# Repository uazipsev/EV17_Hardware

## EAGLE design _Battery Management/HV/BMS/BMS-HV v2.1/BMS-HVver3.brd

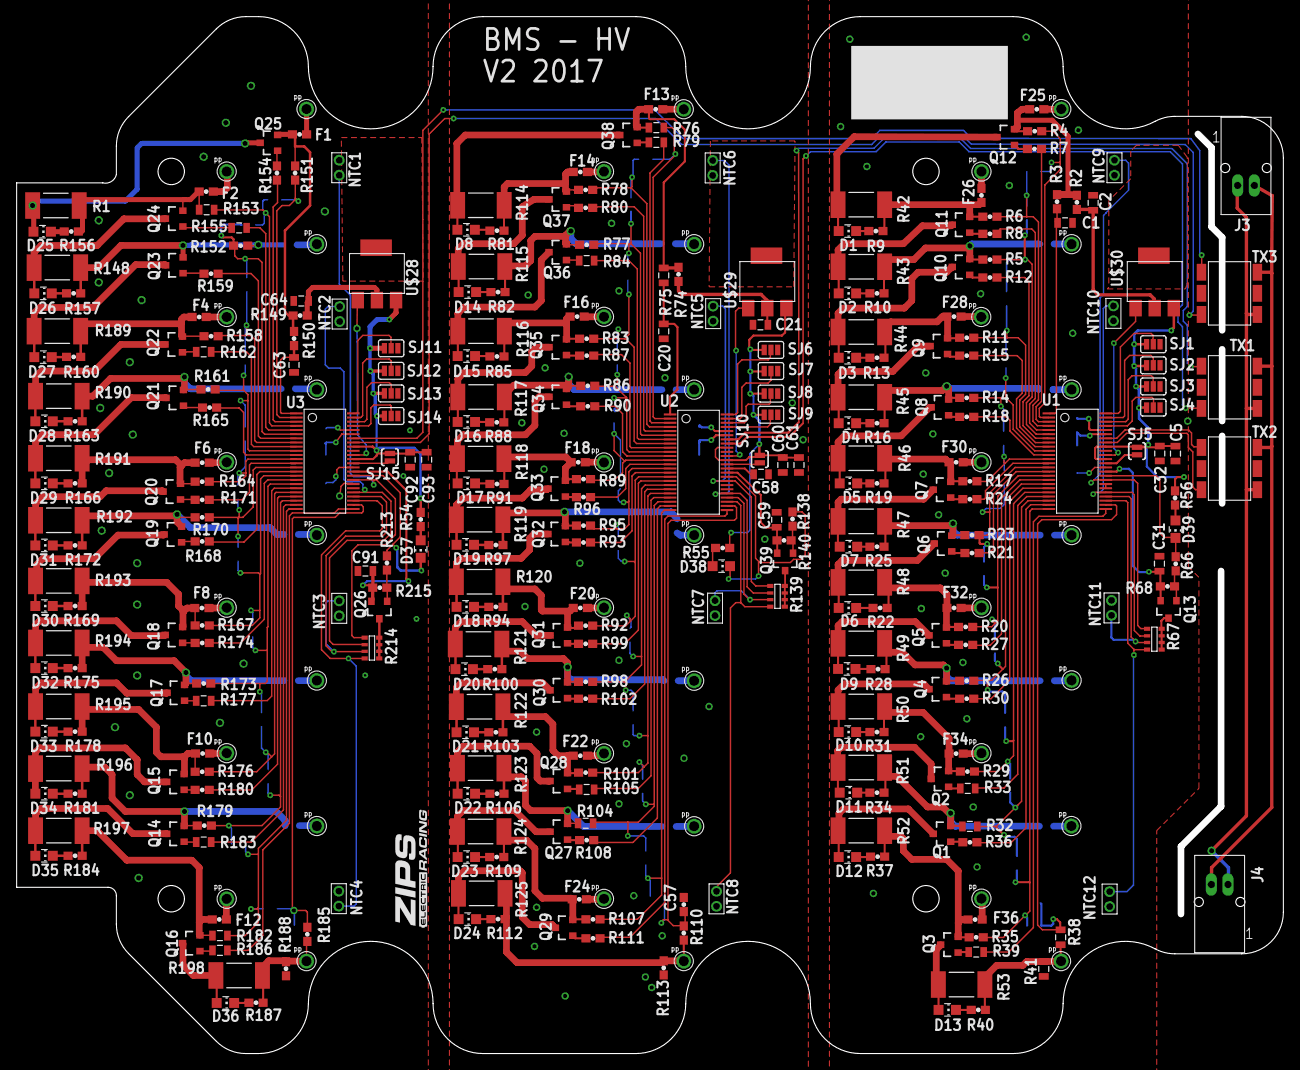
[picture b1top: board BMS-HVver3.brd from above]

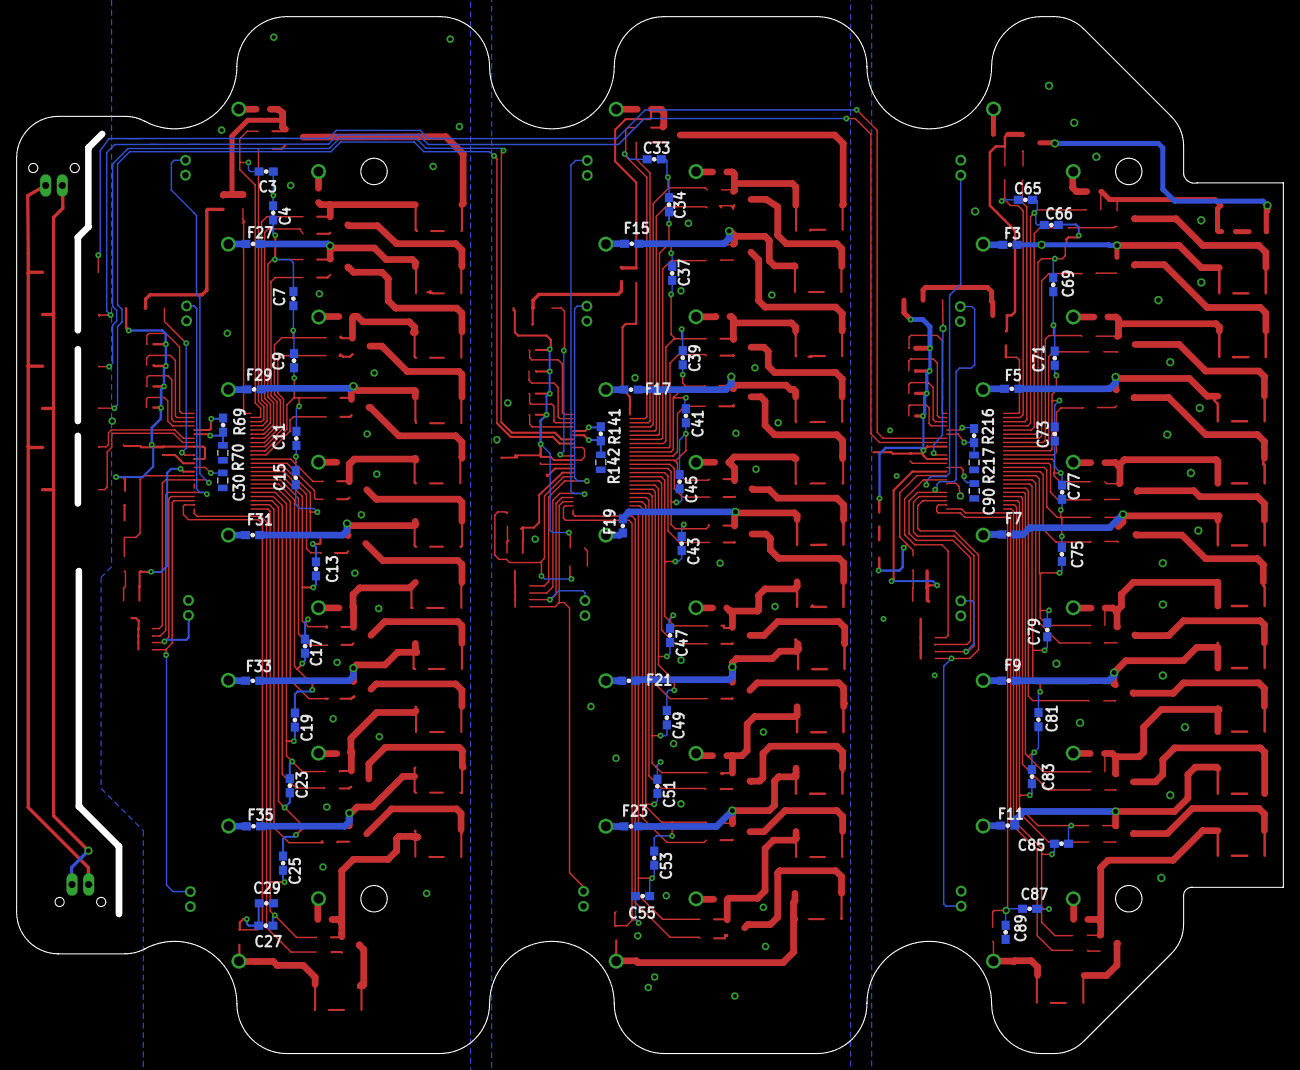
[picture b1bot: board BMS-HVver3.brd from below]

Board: 2 copper layers, 152.4 x 124.8 mm, 423 parts (61 on the bottom side), 332 nets.

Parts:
C1, C2, C20, C21, C63, C64: 0.1UF; 0805
C3, C4, C7, C9, C11, C13, C15, C17, C19, C23, C25, C27, C29, C33, C34, C37, C39, C41, C43, C45, C47, C49, C51, C53, C55, C57, C65, C66, C69, C71, C73, C75, C77, C79, C81, C83, C85, C87, C89: 10NF; 0603
C5, C30, C31, C32, C58, C59, C60, C61, C90, C91, C92, C93: 1UF; 0805
D1, D2, D3, D4, D5, D6, D7, D8, D9, D10, D11, D12, D13, D14, D15, D16, D17, D18, D19, D20, D21, D22, D23, D24, D25, D26, D27, D28, D29, D30, D31, D32, D33, D34, D35, D36: LED_RED; CHIP_LED0805
D37, D38, D39: LED_AMBER; CHIP_LED0805
F1, F2, F3, F4, F5, F6, F7, F8, F9, F10, F11, F12, F13, F14, F15, F16, F17, F18, F19, F20, F21, F22, F23, F24, F25, F26, F27, F28, F29, F30, F31, F32, F33, F34, F35, F36: FUSE_750MA_63V_0603; 0603
J3, J4: M2S02B-PASK-2(LF)(SN); S02B-PASK-2(LF)(SN)
NTC1, NTC2, NTC3, NTC4, NTC5, NTC6, NTC7, NTC8, NTC9, NTC10, NTC11, NTC12: 103JT-025
Q1, Q2, Q3, Q4, Q5, Q6, Q7, Q8, Q9, Q10, Q11, Q12, Q13, Q14, Q15, Q16, Q17, Q18, Q19, Q20, Q21, Q22, Q23, Q24, Q25, Q26, Q27, Q28, Q29, Q30, Q31, Q32, Q33, Q34, Q35, Q36, Q37, Q38, Q39: BSS308PE; SOT23
R1, R42, R43, R44, R45, R46, R47, R48, R49, R50, R51, R52, R53, R114, R115, R116, R117, R118, R119, R120, R121, R122, R123, R124, R125, R148, R189, R190, R191, R192, R193, R194, R195, R196, R197, R198: R2512
R2, R3, R4, R5, R6, R11, R14, R17, R20, R23, R26, R29, R35, R74, R77, R78, R83, R86, R89, R92, R95, R98, R101, R107, R110, R149, R150, R151, R152, R158, R161, R164, R167, R170, R173, R176, R179, R185: 100; 0603
R7, R8, R12, R15, R18, R21, R24, R27, R30, R36, R80, R87, R90, R93, R96, R99, R102, R108, R111, R154, R159, R165, R168, R171, R174, R180: 3.3K; 0603
R9, R10, R13, R16, R19, R22, R25, R28, R31, R34, R37, R40, R81, R82, R85, R88, R91, R94, R97, R100, R103, R106, R109, R112, R156, R157, R160, R163, R166, R169, R172, R175, R178, R181, R184, R187: 475; 0603
R32, R38, R75, R76, R104, R153, R182: 100; 0805
R33, R39, R79, R84, R105, R155, R162, R177, R183, R186: 3.3K; 0805
R41: 0; 0805
R54, R55, R56: 1k; 0603
R66, R138, R213: 1K; 0603
R67, R139, R214: 10K; MNR14
R68, R140, R215: 100K; 0603
R69, R141, R216: 1.2K; 0603
R70, R142, R217: 787; 0805
R113, R188: 0; 0603
SJ1, SJ2, SJ3, SJ4, SJ6, SJ7, SJ8, SJ9, SJ11, SJ12, SJ13, SJ14: PAD-JUMPER-3-NO_YES_SILK
SJ5, SJ10, SJ15: PAD-JUMPER-2-NO_YES_SILK
TX1, TX2, TX3: PE-68386NLT
U1, U2, U3: LTC6804-2; SSOP-48
U$1, U$2, U$3, U$4, U$5, U$6, U$7, U$8, U$9, U$10, U$11, U$12, U$13, U$14, U$15, U$16, U$17, U$18, U$19, U$20, U$21, U$22, U$23, U$24, U$25, U$26, U$40, U$41, U$42, U$43, U$44, U$45, U$46, U$47, U$48, U$49, U$50, U$51, U$52: POGOPIN
U$27: LOGO16-2-L; 2016-2-LOGO-L
U$28, U$29, U$30: NSV1C201MZ4T1G; SOT223

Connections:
A0: SJ9.2, U2.45
A1: SJ8.2, U2.46
A2: SJ7.2, U2.47
A3: SJ6.2, U2.48
A4: SJ4.2, U1.45
A5: SJ3.2, U1.46
A6: SJ2.2, U1.47
A7: SJ1.2, U1.48
A8: SJ14.2, U3.45
A9: SJ13.2, U3.46
A10: SJ12.2, U3.47
A11: SJ11.2, U3.48
C0: C55.2, C57.1, R110.2, U2.26
C1: C53.2, C55.1, R107.2, U2.24
C2: C51.2, C53.1, R104.2, U2.22
C3: C49.2, C51.1, R101.2, U2.20
C4: C47.2, C49.1, R98.2, U2.18
C5: C43.2, C47.1, R92.2, U2.16
C6: C43.1, C45.2, R95.2, U2.14
C7: C41.2, C45.1, R89.2, U2.12
C8: C39.2, C41.1, R86.2, U2.10
C9: C37.2, C39.1, R83.2, U2.8
C10: C34.2, C37.1, R77.2, U2.6
C11: C33.2, C34.1, R78.2, U2.4
C12: C33.1, R76.2, U2.2
C13: C3.1, R4.2, U1.2
C14: C3.2, C4.1, R6.2, U1.4
C15: C7.2, C9.1, R11.2, U1.8
C16: C11.2, C15.1, R17.2, U1.12
C17: C13.1, C15.2, R23.2, U1.14
C18: C13.2, C17.1, R20.2, U1.16
C19: C19.2, C23.1, R29.2, U1.20
C20: C23.2, C25.1, R32.2, U1.22
C21: C25.2, C27.1, R35.2, U1.24
C22: C4.2, C7.1, R5.2, U1.6
C23: C27.2, C29.1, R38.2, U1.26
C24: C17.2, C19.1, R26.2, U1.18
C25: C9.2, C11.1, R14.2, U1.10
C26: C65.1, R151.2, U3.2
C27: C65.2, C66.1, R153.2, U3.4
C28: C69.2, C71.1, R158.2, U3.8
C29: C73.2, C77.1, R164.2, U3.12
C30: C75.1, C77.2, R170.2, U3.14
C31: C75.2, C79.1, R167.2, U3.16
C32: C81.2, C83.1, R176.2, U3.20
C33: C83.2, C85.1, R179.2, U3.22
C34: C85.2, C87.1, R182.2, U3.24
C35: C66.2, C69.1, R152.2, U3.6
C36: C87.2, C89.1, R185.2, U3.26
C37: C79.2, C81.1, R173.2, U3.18
C38: C71.2, C73.1, R161.2, U3.10
DRIVE: U2.38, U$29.P$1
DRIVE1: U1.38, U$30.P$1
DRIVE2: U3.38, U$28.P$1
GND: C63.2, C64.2, C89.2, C90.2, C91.2, C92.2, C93.2, NTC1.1, NTC2.1, NTC3.1, NTC4.1, R188.2, R217.1, SJ11.3, SJ12.3, SJ13.3, SJ14.3, U3.30, U3.31
GNDA: C20.2, C21.2, C57.2, C58.2, C59.2, C60.2, C61.2, NTC5.1, NTC6.1, NTC7.1, R113.2, R142.1, SJ6.3, SJ7.3, SJ8.3, SJ9.3, U2.30, U2.31
GNDI: C1.2, C2.2, C5.2, C29.2, C30.2, C31.2, C32.2, NTC9.1, NTC10.1, NTC11.1, NTC12.1, R41.2, R70.1, SJ1.3, SJ2.3, SJ3.3, SJ4.3, U1.30, U1.31
GPIO1: NTC8.2, R139.4, U2.27
GPIO2: NTC7.2, R139.3, U2.28
GPIO3: NTC6.2, R139.2, U2.29
GPIO4: NTC5.2, R139.1, U2.32
GPIO5: D38.C, R138.2, U2.33
GPIO6: NTC10.2, R67.2, U1.29
GPIO7: NTC9.2, R67.1, U1.32
GPIO8: NTC12.2, R67.4, U1.27
GPIO9: NTC11.2, R67.3, U1.28
GPIO10: D39.C, R66.2, U1.33
GPIO11: NTC2.2, R214.2, U3.29
GPIO12: NTC1.2, R214.1, U3.32
GPIO13: NTC4.2, R214.4, U3.27
GPIO14: NTC3.2, R214.3, U3.28
GPIO15: D37.C, R213.2, U3.33
IBIAS: R141.2, U2.44
IBIAS1: R69.2, U1.44
IBIAS2: R216.2, U3.44
ICMP: R141.1, R142.2, U2.43
ICMP1: R69.1, R70.2, U1.43
ICMP2: R216.1, R217.2, U3.43
IMA: TX1.3, U2.41
IMA1: TX2.3, U1.41
IMA2: TX3.3, U3.41
IPA: TX1.1, U2.42
IPA1: TX2.1, U1.42
IPA2: TX3.1, U3.42
unnamed: Q12.1, R7.1
unnamed: D1.A, Q12.3, R42.2
unnamed: D1.C, R9.2
unnamed: F26.2, Q11.2, R6.1, R9.1, R42.1
unnamed: Q11.1, R8.1
unnamed: D2.A, Q11.3, R43.2
unnamed: D2.C, R10.2
unnamed: F27.2, Q10.2, R5.1, R10.1, R43.1
unnamed: Q10.1, R12.1
unnamed: D3.A, Q10.3, R44.2
unnamed: D3.C, R13.2
unnamed: F28.2, Q9.2, R11.1, R13.1, R44.1
unnamed: Q9.1, R15.1
unnamed: D4.A, Q9.3, R45.2
unnamed: D4.C, R16.2
unnamed: F29.2, Q8.2, R14.1, R16.1, R45.1
unnamed: Q8.1, R18.1
unnamed: D5.A, Q8.3, R46.2
unnamed: D5.C, R19.2
unnamed: Q6.1, R21.1
unnamed: D6.A, Q6.3, R48.2
unnamed: D6.C, R22.2
unnamed: F30.2, Q7.2, R17.1, R19.1, R46.1
unnamed: Q7.1, R24.1
unnamed: D7.A, Q7.3, R47.2
unnamed: D7.C, R25.2
unnamed: F31.2, Q6.2, R23.1, R25.1, R47.1
unnamed: F32.2, Q5.2, R20.1, R22.1, R48.1
unnamed: Q5.1, R27.1
unnamed: D9.A, Q5.3, R49.2
unnamed: D9.C, R28.2
unnamed: F33.2, Q4.2, R26.1, R28.1, R49.1
unnamed: Q4.1, R30.1
unnamed: D10.A, Q4.3, R50.2
unnamed: D10.C, R31.2
unnamed: F34.2, Q2.2, R29.1, R31.1, R50.1
unnamed: Q2.1, R33.1
unnamed: D11.A, Q2.3, R51.2
unnamed: D11.C, R34.2
unnamed: F35.2, Q1.2, R32.1, R34.1, R51.1
unnamed: Q1.1, R36.1
unnamed: D12.A, Q1.3, R52.2
unnamed: D12.C, R37.2
unnamed: Q3.1, R39.1
unnamed: D13.C, R40.2
unnamed: F25.2, Q12.2, R2.1, R3.1, R4.1
unnamed: D13.A, Q3.3, R53.2
unnamed: R38.1, R40.1, R41.1, R53.1, U$1.1
unnamed: F36.2, Q3.2, R35.1, R37.1, R52.1
unnamed: C2.1, R2.2, U$30.P$2
unnamed: Q13.3, R67.5, R67.6, R67.7, R67.8
unnamed: Q13.1, R66.1, R68.1
unnamed: Q25.1, R154.1
unnamed: D25.A, Q25.3, R1.2
unnamed: D25.C, R156.2
unnamed: F2.2, Q24.2, R1.1, R153.1, R156.1
unnamed: Q24.1, R155.1
unnamed: D26.A, Q24.3, R148.2
unnamed: D26.C, R157.2
unnamed: F3.2, Q23.2, R148.1, R152.1, R157.1
unnamed: Q23.1, R159.1
unnamed: D27.A, Q23.3, R189.2
unnamed: D27.C, R160.2
unnamed: F4.2, Q22.2, R158.1, R160.1, R189.1
unnamed: Q22.1, R162.1
unnamed: D28.A, Q22.3, R190.2
unnamed: D28.C, R163.2
unnamed: F5.2, Q21.2, R161.1, R163.1, R190.1
unnamed: Q21.1, R165.1
unnamed: D29.A, Q21.3, R191.2
unnamed: D29.C, R166.2
unnamed: Q19.1, R168.1
unnamed: D30.A, Q19.3, R193.2
unnamed: D30.C, R169.2
unnamed: F6.2, Q20.2, R164.1, R166.1, R191.1
unnamed: Q20.1, R171.1
unnamed: D31.A, Q20.3, R192.2
unnamed: D31.C, R172.2
unnamed: F7.2, Q19.2, R170.1, R172.1, R192.1
unnamed: F8.2, Q18.2, R167.1, R169.1, R193.1
unnamed: Q18.1, R174.1
unnamed: D32.A, Q18.3, R194.2
unnamed: D32.C, R175.2
unnamed: F9.2, Q17.2, R173.1, R175.1, R194.1
unnamed: Q17.1, R177.1
unnamed: D33.A, Q17.3, R195.2
unnamed: D33.C, R178.2
unnamed: F10.2, Q15.2, R176.1, R178.1, R195.1
unnamed: Q15.1, R180.1
unnamed: D34.A, Q15.3, R196.2
unnamed: D34.C, R181.2
unnamed: F11.2, Q14.2, R179.1, R181.1, R196.1
unnamed: Q14.1, R183.1
unnamed: D35.A, Q14.3, R197.2
unnamed: D35.C, R184.2
unnamed: Q16.1, R186.1
unnamed: D36.C, R187.2
unnamed: F1.2, Q25.2, R149.1, R150.1, R151.1
unnamed: D36.A, Q16.3, R198.2
unnamed: Q38.1, R79.1
unnamed: D8.A, Q38.3, R114.2
unnamed: D8.C, R81.2
unnamed: R185.1, R187.1, R188.1, R198.1, U$14.1
unnamed: F12.2, Q16.2, R182.1, R184.1, R197.1
unnamed: C64.1, R149.2, U$28.P$2
unnamed: F14.2, Q37.2, R78.1, R81.1, R114.1
unnamed: D37.A, R54.1
unnamed: Q37.1, R80.1
unnamed: D14.A, Q37.3, R115.2
unnamed: D14.C, R82.2
unnamed: F15.2, Q36.2, R77.1, R82.1, R115.1
unnamed: Q26.3, R214.5, R214.6, R214.7, R214.8
unnamed: Q36.1, R84.1
unnamed: D15.A, Q36.3, R116.2
unnamed: D15.C, R85.2
unnamed: F16.2, Q35.2, R83.1, R85.1, R116.1
unnamed: Q26.1, R213.1, R215.1
unnamed: D38.A, R55.1
unnamed: Q35.1, R87.1
unnamed: D16.A, Q35.3, R117.2
unnamed: D16.C, R88.2
unnamed: F17.2, Q34.2, R86.1, R88.1, R117.1
unnamed: J3.2, J4.2, TX1.6, TX2.6, TX3.6
unnamed: Q34.1, R90.1
unnamed: D17.A, Q34.3, R118.2
unnamed: D17.C, R91.2
unnamed: J3.1, J4.1, TX1.4, TX2.4, TX3.4
unnamed: Q32.1, R93.1
unnamed: D18.A, Q32.3, R120.2
unnamed: D18.C, R94.2
unnamed: C90.1, U3.35
unnamed: F18.2, Q33.2, R89.1, R91.1, R118.1
unnamed: C30.1, U1.35
unnamed: Q33.1, R96.1
unnamed: D19.A, Q33.3, R119.2
unnamed: D19.C, R97.2
unnamed: F19.2, Q32.2, R95.1, R97.1, R119.1
unnamed: D39.A, R56.1
unnamed: F20.2, Q31.2, R92.1, R94.1, R120.1
unnamed: Q31.1, R99.1
unnamed: D20.A, Q31.3, R121.2
unnamed: D20.C, R100.2
unnamed: F21.2, Q30.2, R98.1, R100.1, R121.1
unnamed: Q30.1, R102.1
unnamed: D21.A, Q30.3, R122.2
unnamed: D21.C, R103.2
unnamed: F22.2, Q28.2, R101.1, R103.1, R122.1
unnamed: Q28.1, R105.1
unnamed: D22.A, Q28.3, R123.2
unnamed: D22.C, R106.2
unnamed: F23.2, Q27.2, R104.1, R106.1, R123.1
unnamed: Q27.1, R108.1
unnamed: D23.A, Q27.3, R124.2
unnamed: D23.C, R109.2
unnamed: Q29.1, R111.1
unnamed: D24.C, R112.2
unnamed: F13.2, Q38.2, R74.1, R75.1, R76.1
unnamed: D24.A, Q29.3, R125.2
unnamed: R110.1, R112.1, R113.1, R125.1, U$40.1
unnamed: F24.2, Q29.2, R107.1, R109.1, R124.1
unnamed: C21.1, R74.2, U$29.P$2
unnamed: Q39.3, R139.5, R139.6, R139.7, R139.8
unnamed: Q39.1, R138.1, R140.1
unnamed: F12.1, U$15.1
unnamed: F11.1, U$16.1
unnamed: F10.1, U$17.1
unnamed: F9.1, U$18.1
unnamed: F8.1, U$19.1
unnamed: F7.1, U$20.1
unnamed: F6.1, U$21.1
unnamed: F5.1, U$22.1
unnamed: F4.1, U$23.1
unnamed: F3.1, U$24.1
unnamed: F2.1, U$25.1
unnamed: F1.1, U$26.1
unnamed: F24.1, U$41.1
unnamed: F23.1, U$42.1
unnamed: F22.1, U$43.1
unnamed: F21.1, U$44.1
unnamed: F20.1, U$45.1
unnamed: F19.1, U$46.1
unnamed: F18.1, U$47.1
unnamed: F17.1, U$48.1
unnamed: F16.1, U$49.1
unnamed: F15.1, U$50.1
unnamed: F14.1, U$51.1
unnamed: F13.1, U$52.1
unnamed: F36.1, U$2.1
unnamed: F35.1, U$3.1
unnamed: F34.1, U$4.1
unnamed: F33.1, U$5.1
unnamed: F32.1, U$6.1
unnamed: F31.1, U$7.1
unnamed: F30.1, U$8.1
unnamed: F29.1, U$9.1
unnamed: F28.1, U$10.1
unnamed: F27.1, U$11.1
unnamed: F26.1, U$12.1
unnamed: F25.1, U$13.1
S1: R111.2, U2.25
S2: R108.2, U2.23
S3: R105.2, U2.21
S4: R102.2, U2.19
S5: R99.2, U2.17
S6: R93.2, U2.15
S7: R96.2, U2.13
S8: R90.2, U2.11
S9: R87.2, U2.9
S10: R84.2, U2.7
S11: R80.2, U2.5
S12: R79.2, U2.3
S13: R7.2, U1.3
S14: R8.2, U1.5
S15: R12.2, U1.7
S16: R15.2, U1.9
S17: R18.2, U1.11
S18: R21.2, U1.15
S19: R24.2, U1.13
S20: R27.2, U1.17
S21: R30.2, U1.19
S22: R33.2, U1.21
S23: R36.2, U1.23
S24: R39.2, U1.25
S25: R154.2, U3.3
S26: R155.2, U3.5
S27: R159.2, U3.7
S28: R162.2, U3.9
S29: R165.2, U3.11
S30: R168.2, U3.15
S31: R171.2, U3.13
S32: R174.2, U3.17
S33: R177.2, U3.19
S34: R180.2, U3.21
S35: R183.2, U3.23
S36: R186.2, U3.25
SWTEN: SJ10.1, U2.36
SWTEN1: SJ5.1, U1.36
SWTEN2: SJ15.1, U3.36
V+: C20.1, R75.2, U2.1
V+1: C1.1, R3.2, U1.1
V+2: C63.1, R150.2, U3.1
VREF1: C58.1, U2.35
VREF2: C59.1, Q39.2, R140.2, U2.34
VREF4: C31.1, Q13.2, R68.2, U1.34
VREF6: C91.1, Q26.2, R215.2, U3.34
VREG: C60.1, C61.1, R55.2, SJ6.1, SJ7.1, SJ8.1, SJ9.1, SJ10.2, U2.37, U2.40, U$29.P$3
VREG1: C5.1, C32.1, R56.2, SJ1.1, SJ2.1, SJ3.1, SJ4.1, SJ5.2, U1.37, U1.40, U$30.P$3
VREG2: C92.1, C93.1, R54.2, SJ11.1, SJ12.1, SJ13.1, SJ14.1, SJ15.2, U3.37, U3.40, U$28.P$3

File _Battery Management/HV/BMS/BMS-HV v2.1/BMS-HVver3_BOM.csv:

Qty-1,Part References,Value,Package,Mfg Part Num,Mfg Name,VID,Vendor Part Num,Description,Pkg Code,XREF
3,"SJ5, SJ10, SJ15",,PAD-JUMPER-2-NO_YES_SILK,***PART# '*' NOT FOUND***,*,*,*,*,*,*
12,"SJ1, SJ2, SJ3, SJ4, SJ6, SJ7, SJ8, SJ9, SJ11, SJ12, SJ13, SJ14",,PAD-JUMPER-3-NO_YES_SILK,***PART# '*' NOT FOUND***,*,*,*,*,*,*
36,"R1, R42, R43, R44, R45, R46, R47, R48, R49, R50, R51, R52, R53, R114, R115, R116, R117, R118, R119, R120, R121, R122, R123, R124, R125, R148, R189, R190, R191, R192, R193, R194, R195, R196, R197, R198",,R2512,***PART# '*' NOT FOUND***,*,*,*,*,*,*
2,"R113, R188",0,0603,CRCW06030000Z0EA,Vishay Dale,DK,541-0.0GCT-ND,RES SMD 0.0OHM JUMPER 1/10W 0603,0603 (1608 Metric),REF167
1,"R41",0,0805,RC0805JR-070RL,Yageo,DK,311-0.0ARCT-ND,RES SMD 0.0 OHM JUMPER 1/8W 0805,0805 (2012 Metric),REF310
6,"C1, C2, C20, C21, C63, C64",0.1UF,0805,CL21B104KCC5PNC,Samsung Electro-Mechanics America, Inc.,DK,1276-2447-1-ND,CAP CER 0.1UF 100V X7R 0805,0805 (2012 Metric),REF253
3,"R69, R141, R216",1.2K,0603,RC0603JR-071K2L,Yageo,DK,311-1.2KGRCT-ND,RES SMD 1.2K OHM 5% 1/10W 0603,0603 (1608 Metric),REF88
3,"R66, R138, R213",1K,0603,RC0603JR-071KL,Yageo,DK,311-1.0KGRCT-ND,RES SMD 1K OHM 5% 1/10W 0603,0603 (1608 Metric),REF84
12,"C5, C30, C31, C32, C58, C59, C60, C61, C90, C91, C92, C93",1UF,0805,UMK212F105ZG-T,Taiyo Yuden,DK,587-1308-1-ND,CAP CER 1UF 50V Y5V 0805,0805 (2012 Metric),REF17
3,"R54, R55, R56",1k,0603,RC0603JR-071KL,Yageo,DK,311-1.0KGRCT-ND,RES SMD 1K OHM 5% 1/10W 0603,0603 (1608 Metric),REF84
26,"R7, R8, R12, R15, R18, R21, R24, R27, R30, R36, R80, R87, R90, R93, R96, R99, R102, R108, R111, R154, R159, R165, R168, R171, R174, R180",3.3K,0603,RC0603JR-073K3L,Yageo,DK,311-3.3KGRCT-ND,RES SMD 3.3K OHM 5% 1/10W 0603,0603 (1608 Metric),REF89
10,"R33, R39, R79, R84, R105, R155, R162, R177, R183, R186",3.3K,0805,RC0805FR-073K3L,Yageo,DK,311-3.30KCRCT-ND,RES SMD 3.3K OHM 1% 1/8W 0805,0805 (2012 Metric),REF128
3,"R67, R139, R214",10K,MNR14,MNR14ERAPJ103,Rohm Semiconductor,DK,RHM1596CT-ND,RES ARRAY 4 RES 10K OHM 1206,1206 (3216 Metric), Convex, Long Side Terminals,REF29
39,"C3, C4, C7, C9, C11, C13, C15, C17, C19, C23, C25, C27, C29, C33, C34, C37, C39, C41, C43, C45, C47, C49, C51, C53, C55, C57, C65, C66, C69, C71, C73, C75, C77, C79, C81, C83, C85, C87, C89",10NF,0603,CL10B103KC8NNNC,Samsung Electro-Mechanics America, Inc.,DK,1276-1196-1-ND,CAP CER 10000PF 100V X7R 0603,0603 (1608 Metric),REF160
38,"R2, R3, R4, R5, R6, R11, R14, R17, R20, R23, R26, R29, R35, R74, R77, R78, R83, R86, R89, R92, R95, R98, R101, R107, R110, R149, R150, R151, R152, R158, R161, R164, R167, R170, R173, R176, R179, R185",100,0603,RC0603FR-07100RL,Yageo,DK,311-100HRCT-ND,RES SMD 100 OHM 1% 1/10W 0603,0603 (1608 Metric),REF159
7,"R32, R38, R75, R76, R104, R153, R182",100,0805,RC0805FR-07100RL,Yageo,DK,311-100CRCT-ND,RES SMD 100 OHM 1% 1/8W 0805,0805 (2012 Metric),REF307
3,"R68, R140, R215",100K,0603,RC0603JR-07100KL,Yageo,DK,311-100KGRCT-ND,RES SMD 100K OHM 5% 1/10W 0603,0603 (1608 Metric),REF90
12,"NTC1, NTC2, NTC3, NTC4, NTC5, NTC6, NTC7, NTC8, NTC9, NTC10, NTC11, NTC12",103JT-025,103JT-025,***PART# '*' NOT FOUND***,*,*,*,*,*,*
36,"R9, R10, R13, R16, R19, R22, R25, R28, R31, R34, R37, R40, R81, R82, R85, R88, R91, R94, R97, R100, R103, R106, R109, R112, R156, R157, R160, R163, R166, R169, R172, R175, R178, R181, R184, R187",475,0603,CRCW0201475RFKED,Vishay Dale,DK,541-475AABCT-ND,RES SMD 475 OHM 1% 1/20W 0201,0201 (0603 Metric),REF292
3,"R70, R142, R217",787,0805,RC0805FR-07787RL,Yageo,DK,311-787CRCT-ND,RES SMD 787 OHM 1% 1/8W 0805,0805 (2012 Metric),REF183
39,"Q1, Q2, Q3, Q4, Q5, Q6, Q7, Q8, Q9, Q10, Q11, Q12, Q13, Q14, Q15, Q16, Q17, Q18, Q19, Q20, Q21, Q22, Q23, Q24, Q25, Q26, Q27, Q28, Q29, Q30, Q31, Q32, Q33, Q34, Q35, Q36, Q37, Q38, Q39",BSS308PE,SOT23,BSS308PE H6327,Infineon Technologies,DK,BSS308PE H6327CT-ND,MOSFET P-CH 30V 2A SOT23,SOT-23-3,REF291
36,"F1, F2, F3, F4, F5, F6, F7, F8, F9, F10, F11, F12, F13, F14, F15, F16, F17, F18, F19, F20, F21, F22, F23, F24, F25, F26, F27, F28, F29, F30, F31, F32, F33, F34, F35, F36",FUSE_750MA_63V_0603,0603,C2Q 750,Bel Fuse Inc.,DK,507-1090-1-ND,FUSE BOARD MNT 750MA 32VAC 63VDC,0603 (1608 Metric),REF309
3,"D37, D38, D39",LED_AMBER,CHIP_LED0805,HSMA-C170,Avago Technologies US Inc.,DK,516-1431-1-ND,LED AMBER DIFFUSED 0805 SMD,0805 (2012 Metric),REF39
36,"D1, D2, D3, D4, D5, D6, D7, D8, D9, D10, D11, D12, D13, D14, D15, D16, D17, D18, D19, D20, D21, D22, D23, D24, D25, D26, D27, D28, D29, D30, D31, D32, D33, D34, D35, D36",LED_RED,CHIP_LED0805,LH R974-LP-1,OSRAM Opto Semiconductors Inc.,DK,475-1415-1-ND,LED RED DIFFUSED 0805 SMD,0805 (2012 Metric),REF36
1,"U$27",LOGO16-2-L,2016-2-LOGO-L,***PART# '*' NOT FOUND***,*,*,*,*,*,*
3,"U1, U2, U3",LTC6804-2,SSOP-48,LTC6804IG-2#PBF,Linear Technology,DK,LTC6804IG-2#PBF-ND,IC MONITOR BATT STACK 48SSOP,48-FSOP (0.209", 5.30mm Width),REF215
2,"J3, J4",M2S02B-PASK-2(LF)(SN),S02B-PASK-2(LF)(SN),***PART# 'S02B-PASK-2(LF)(SN)' NOT FOUND***,*,*,*,*,*,*
3,"U$28, U$29, U$30",NSV1C201MZ4T1G,SOT223,***PART# 'NSV1C201MZ4T1G' NOT FOUND***,*,*,*,*,*,*
3,"TX1, TX2, TX3",PE-68386NLT,PE-68386NLT,PE-68386NLT,Pulse Electronics Corporation,DK,553-1776-1-ND,XFRMR GATE DRIVE 1:1 785UH SMD,None,REF166
39,"U$1, U$2, U$3, U$4, U$5, U$6, U$7, U$8, U$9, U$10, U$11, U$12, U$13, U$14, U$15, U$16, U$17, U$18, U$19, U$20, U$21, U$22, U$23, U$24, U$25, U$26, U$40, U$41, U$42, U$43, U$44, U$45, U$46, U$47, U$48, U$49, U$50, U$51, U$52",POGOPIN,POGOPIN,***PART# '*' NOT FOUND***,*,*,*,*,*,*

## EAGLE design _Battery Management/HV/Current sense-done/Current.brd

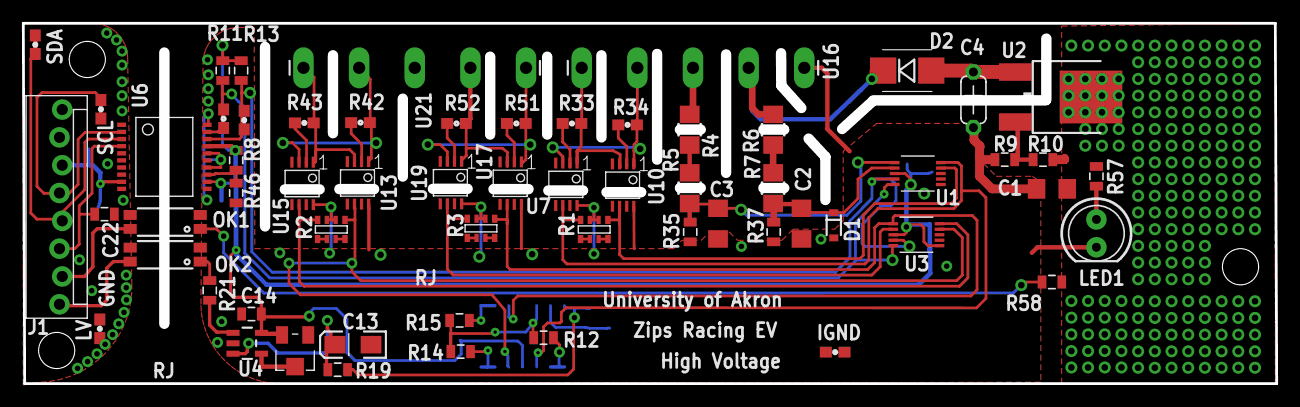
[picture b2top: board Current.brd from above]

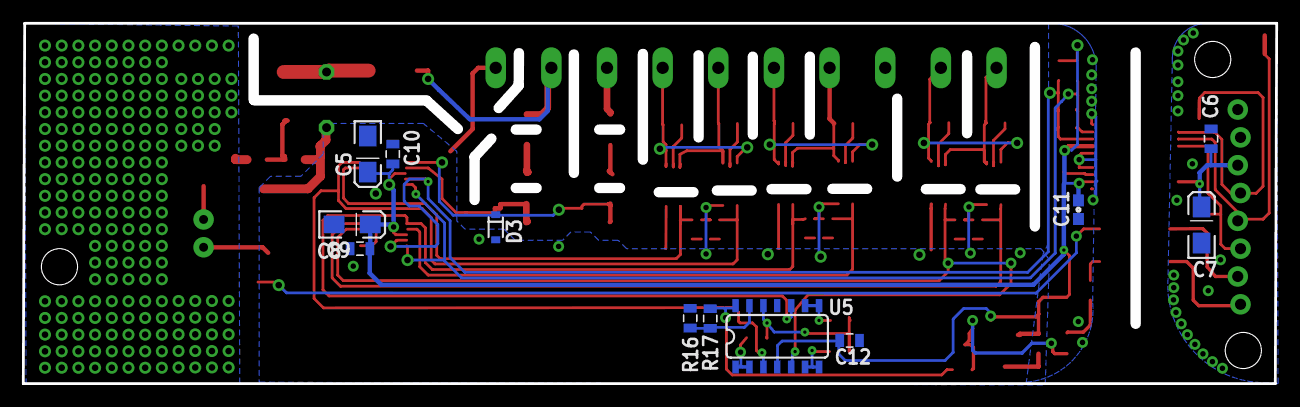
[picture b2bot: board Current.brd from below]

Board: 2 copper layers, 114.4 x 32.9 mm, 77 parts (12 on the bottom side), 57 nets.

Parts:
C1, C2, C3: 10UF; 1206@1
C4: 0.47UF; C_TH_05-02
C5, C7, C9, C13: 10UF; EIA3216-16V
C6, C8, C10, C12, C14, C22: 0.1UF; 0805
C11: 0.01UF; 0603
D1, D3: 3.3V; SOD-323
D2: DIODE-ZENER_56V; SMB
GND: TPSMD; 0603
IGND: TPSMD; 0603
ISCL: TPSMD; 0603
ISDA: TPSMD; 0603
J1: M80022232081-2; MOLEX-1X8-2
LED1: LED5MM
OK1, OK2: TCMT1103; SOP-4
POT1: 22AR100KLFTR
R1, R2, R3: 100K; MNR14
R4, R5, R6, R7: 174k; 1206
R8: 30.9K; 0805
R9: 18.2K; 0805
R10: 6.04k; 0805
R11, R13, R17, R35, R37: 2.2K; 0805
R12, R14, R15, R16, R21, R57, R58: 1K; 0805
R19, R46: 10K; 0805
R33, R34, R42, R43, R51, R52: 4.99K; 0603
SCL: TPSMD; 0603
SDA: TPSMD; 0603
STANDOFF1, STANDOFF2, STANDOFF3: STAND-OFF
U1, U3: ADS1015; MSOP-10
U2: LR8; DPAK
U4: OPA344; SOT23-5
U5: MCP6L04; SO-14
U6: ADM3260ARSZ-RL7; SSOP-20
U7, U10, U13, U15, U17, U19: HV7802; MSOP-8
U16, U21: M5_0.2_ISO; 1X9_0.1_SP
U$2: LOGO16-M; 2016-LOGO-M

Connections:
5V: C1.1, R10.2, R57.1, R58.1, U2.2
+3V3: C22.1, J1.3, U6.4
+5V: C6.1, C7.A, J1.6, U6.9
CRNT1A: R1.8, U1.5, U5.3, U7.6
CRNT1B: R1.5, U1.4, U10.6
CRNT2A: R2.5, U3.4, U5.5, U13.6
CRNT2B: R2.8, U3.5, U15.6
CRNT3A: R3.5, U3.6, U5.10, U17.6
CRNT3B: R3.8, U3.7, U19.6
GND: C6.2, C7.C, C22.2, GND.1, GND.2, J1.7, J1.8, OK1.3, OK2.3, U6.1, U6.5, U6.7, U6.8, U6.10
HV+: C4.1, D2.A, U2.1
unnamed: R3.3, R3.4
unnamed: R3.1, R3.2
unnamed: R2.3, R2.4
unnamed: R2.1, R2.2
unnamed: R1.1, R1.2
unnamed: R1.3, R1.4
unnamed: J1.4, SDA.1, SDA.2, U6.3
unnamed: J1.5, SCL.1, SCL.2, U6.2
unnamed: R4.1, R5.2
unnamed: R6.1, R7.2
unnamed: R12.2, R14.2, R15.2, U5.12
unnamed: R16.2, R17.2, U5.13
unnamed: R17.1, R19.1, U5.14
unnamed: C13.A, R19.2, U4.3
unnamed: OK2.1, R21.1
unnamed: R15.1, U5.8, U5.9
unnamed: R14.1, U5.6, U5.7
unnamed: POT1.2, U4.4
unnamed: R21.2, U4.1
unnamed: R12.1, U5.1, U5.2
unnamed: J1.1, OK2.4
unnamed: R9.2, R10.1, U2.3
unnamed: C5.A, C8.1, C9.A, C10.1, C11.1, C12.1, C14.1, POT1.1, R8.2, R11.2, R13.2, U1.8, U3.1, U3.8, U4.5, U5.4, U6.12, U6.17
unnamed: D2.C, R6.2, U16.7
unnamed: R33.2, U7.1, U10.3, U16.1
unnamed: C3.1, D3.C, R5.1, R35.2, U1.6
unnamed: R34.2, U7.3, U10.1, U16.3
unnamed: R4.2, U16.5
unnamed: R33.1, U7.2
unnamed: R34.1, U10.2
unnamed: LED1.A, R57.2
unnamed: R43.2, U13.3, U15.1, U21.9
unnamed: R42.1, U13.2
unnamed: C2.1, D1.C, R7.1, R37.2, U1.7
unnamed: R43.1, U15.2
unnamed: R42.2, U13.1, U15.3, U21.7
unnamed: OK1.1, R58.2
unnamed: R52.2, U17.3, U19.1, U21.3
unnamed: R51.1, U17.2
unnamed: R52.1, U19.2
unnamed: R51.2, U17.1, U19.3, U21.1
unnamed: ISCL.1, ISCL.2, R11.1, U1.10, U3.10, U6.19
unnamed: ISDA.1, ISDA.2, R13.1, U1.9, U3.9, U6.18
unnamed: R8.1, R46.2, U6.13
TSAL_EN: J1.2, OK1.4
V-: C1.2, C2.2, C3.2, C4.2, C5.C, C8.2, C9.C, C10.2, C11.2, C12.2, C13.C, C14.2, D1.A, D3.A, IGND.1, IGND.2, LED1.K, OK1.2, OK2.2, POT1.3, R1.6, R1.7, R2.6, R2.7, R3.6, R3.7, R9.1, R16.1, R35.1, R37.1, R46.1, U1.1, U1.3, U3.3, U4.2, U5.11, U6.11, U6.14, U6.16, U6.20, U7.8, U10.8, U13.8, U15.8, U16.9, U17.8, U19.8

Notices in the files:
parts and their libraries:
SparkFun-Passives: Licensing: Creative Commons ShareAlike 4.0 International - https://creativecommons.org/licenses/by-sa/4.0
SparkFun-Connectors: Licensing: CC v3.0 Share-Alike You are welcome to use this library for commercial purposes.
